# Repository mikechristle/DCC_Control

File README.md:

# DCC_Control
A project that controls a DCC model train set.
## Python Source for the Pico
The python source files that run on the Raspberry PI Pico to control the DCC signal
## Python Source for the PC Control Program
THe python source files that run on a PC to communicate with the Raspberry PI Pico.
## KiCad PCB Files
KiCad source files for the printed circuit board.
## Sources for the DCC_Monitor application
Sources for a seperate project that will monitor and display the contents of the DCC signal.

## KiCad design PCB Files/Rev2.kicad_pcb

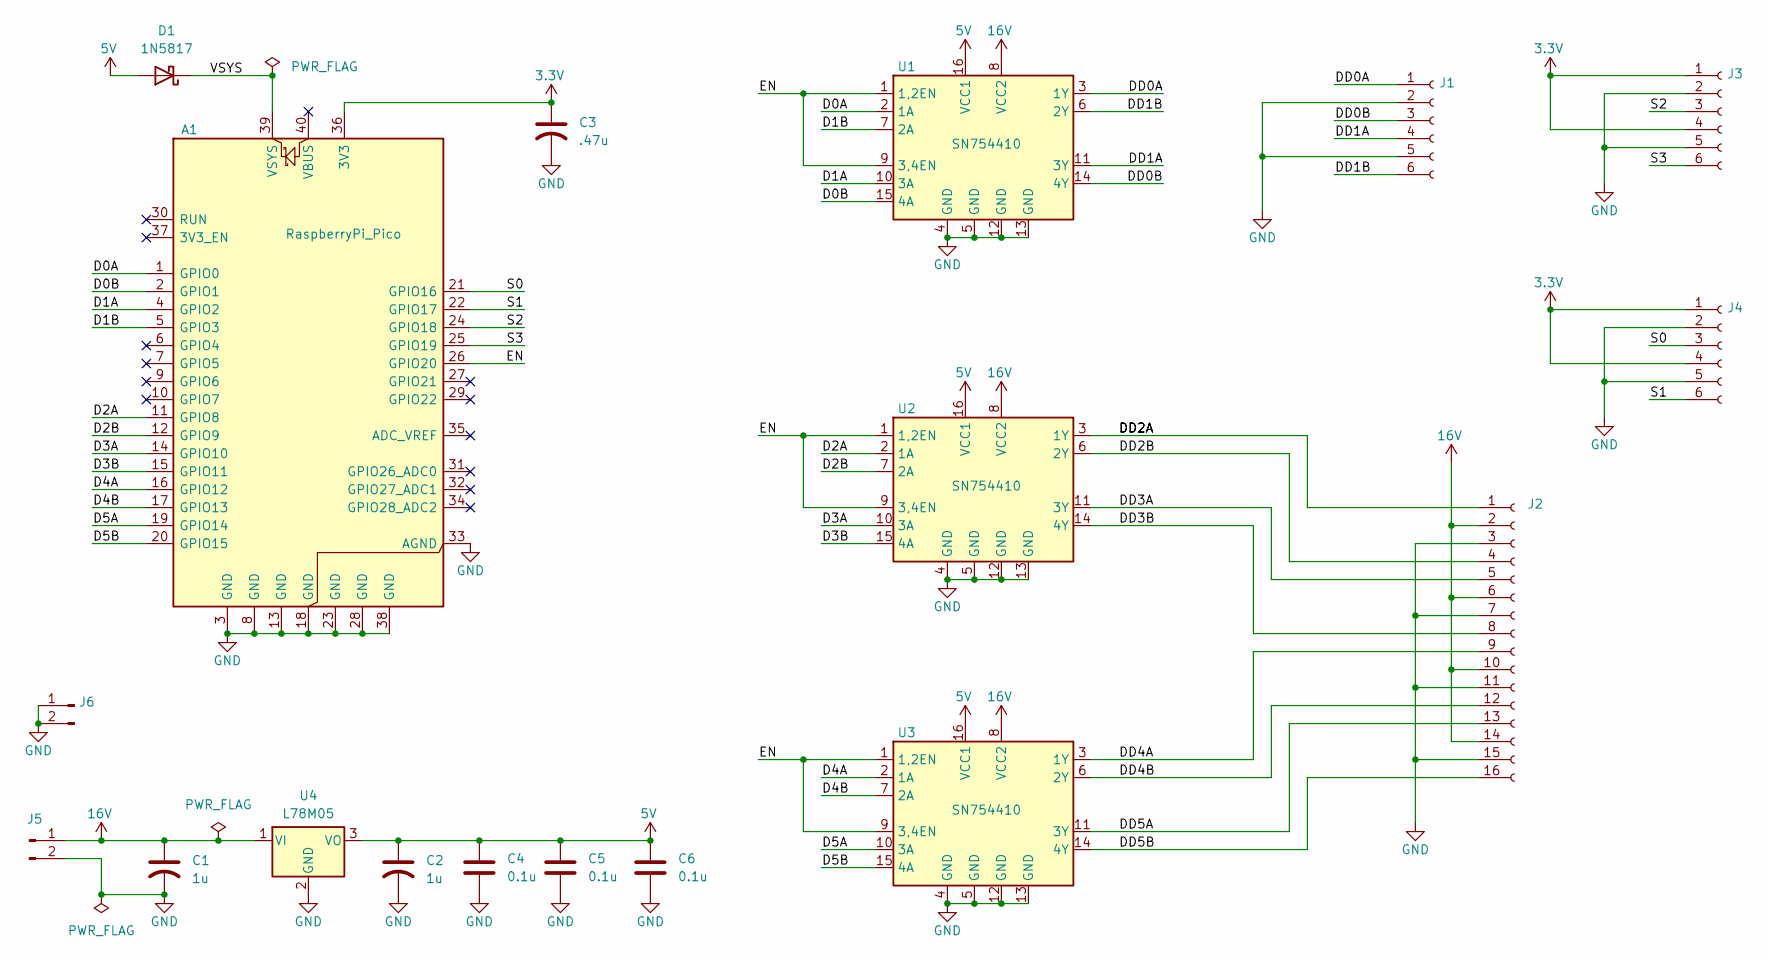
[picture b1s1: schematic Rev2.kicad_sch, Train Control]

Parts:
A1: RaspberryPi_Pico; DIP-40_700_ELL
C1, C2: 1u; CP_Radial_D6.3mm_P2.50mm
C3: .47u; CP_Radial_D6.3mm_P2.50mm
C4, C5, C6: 0.1u; C_Disc_D3.0mm_W1.6mm_P2.50mm
D1: 1N5817; D_A-405_P10.16mm_Horizontal
J1, J3, J4: Conn_01x06_Socket; Phoenix Socket 6
J2: Conn_01x16_Socket; Phoenix Socket 16
J5: 16Vdc; PinHeader_1x02_P2.54mm_Vertical
J6: GND; PinHeader_1x02_P2.54mm_Vertical
U1, U2, U3: SN754410; DIP-16_W7.62mm
U4: L78M05; TO-252-2

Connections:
3.3V: A1.36 (3V3), C3.1, J3.1, J3.4, J4.1, J4.4
5V: C2.1, C4.1, C5.1, C6.1, D1.2 (A), U1.16 (VCC1), U2.16 (VCC1), U3.16 (VCC1), U4.3 (VO)
16V: C1.1, J2.2, J2.6, J2.10, J2.14, J5.1, U1.8 (VCC2), U2.8 (VCC2), U3.8 (VCC2), U4.1 (VI)
/D0A: A1.1 (GPIO0), U1.2 (1A)
/D0B: A1.2 (GPIO1), U1.15 (4A)
/D1A: A1.4 (GPIO2), U1.10 (3A)
/D1B: A1.5 (GPIO3), U1.7 (2A)
/D2A: A1.11 (GPIO8), U2.2 (1A)
/D2B: A1.12 (GPIO9), U2.7 (2A)
/D3A: A1.14 (GPIO10), U2.10 (3A)
/D3B: A1.15 (GPIO11), U2.15 (4A)
/D4A: A1.16 (GPIO12), U3.2 (1A)
/D4B: A1.17 (GPIO13), U3.7 (2A)
/D5A: A1.19 (GPIO14), U3.10 (3A)
/D5B: A1.20 (GPIO15), U3.15 (4A)
/DD0A: J1.1, U1.3 (1Y)
/DD0B: J1.3, U1.14 (4Y)
/DD1A: J1.4, U1.11 (3Y)
/DD1B: J1.6, U1.6 (2Y)
/EN: A1.26 (GPIO20), U1.1 (1,2EN), U1.9 (3,4EN), U2.1 (1,2EN), U2.9 (3,4EN), U3.1 (1,2EN), U3.9 (3,4EN)
/S0: A1.21 (GPIO16), J4.3
/S1: A1.22 (GPIO17), J4.6
/S2: A1.24 (GPIO18), J3.3
/S3: A1.25 (GPIO19), J3.6
GND: A1.3 (GND), A1.8 (GND), A1.13 (GND), A1.18 (GND), A1.23 (GND), A1.28 (GND), A1.33 (AGND), A1.38 (GND), C1.2, C2.2, C3.2, C4.2, C5.2, C6.2, J1.2, J1.5, J2.3, J2.7, J2.11, J2.15, J3.2, J3.5, J4.2, J4.5, J5.2, J6.1, J6.2, U1.4 (GND), U1.5 (GND), U1.12 (GND), U1.13 (GND), U2.4 (GND), U2.5 (GND), U2.12 (GND), U2.13 (GND), U3.4 (GND), U3.5 (GND), U3.12 (GND), U3.13 (GND), U4.2 (GND)
unnamed: A1.39 (VSYS), D1.1 (K)
unnamed: J2.1, U2.3 (1Y)
unnamed: J2.4, U2.6 (2Y)
unnamed: J2.5, U2.11 (3Y)
unnamed: J2.8, U2.14 (4Y)
unnamed: J2.9, U3.3 (1Y)
unnamed: J2.12, U3.6 (2Y)
unnamed: J2.13, U3.11 (3Y)
unnamed: J2.16, U3.14 (4Y)

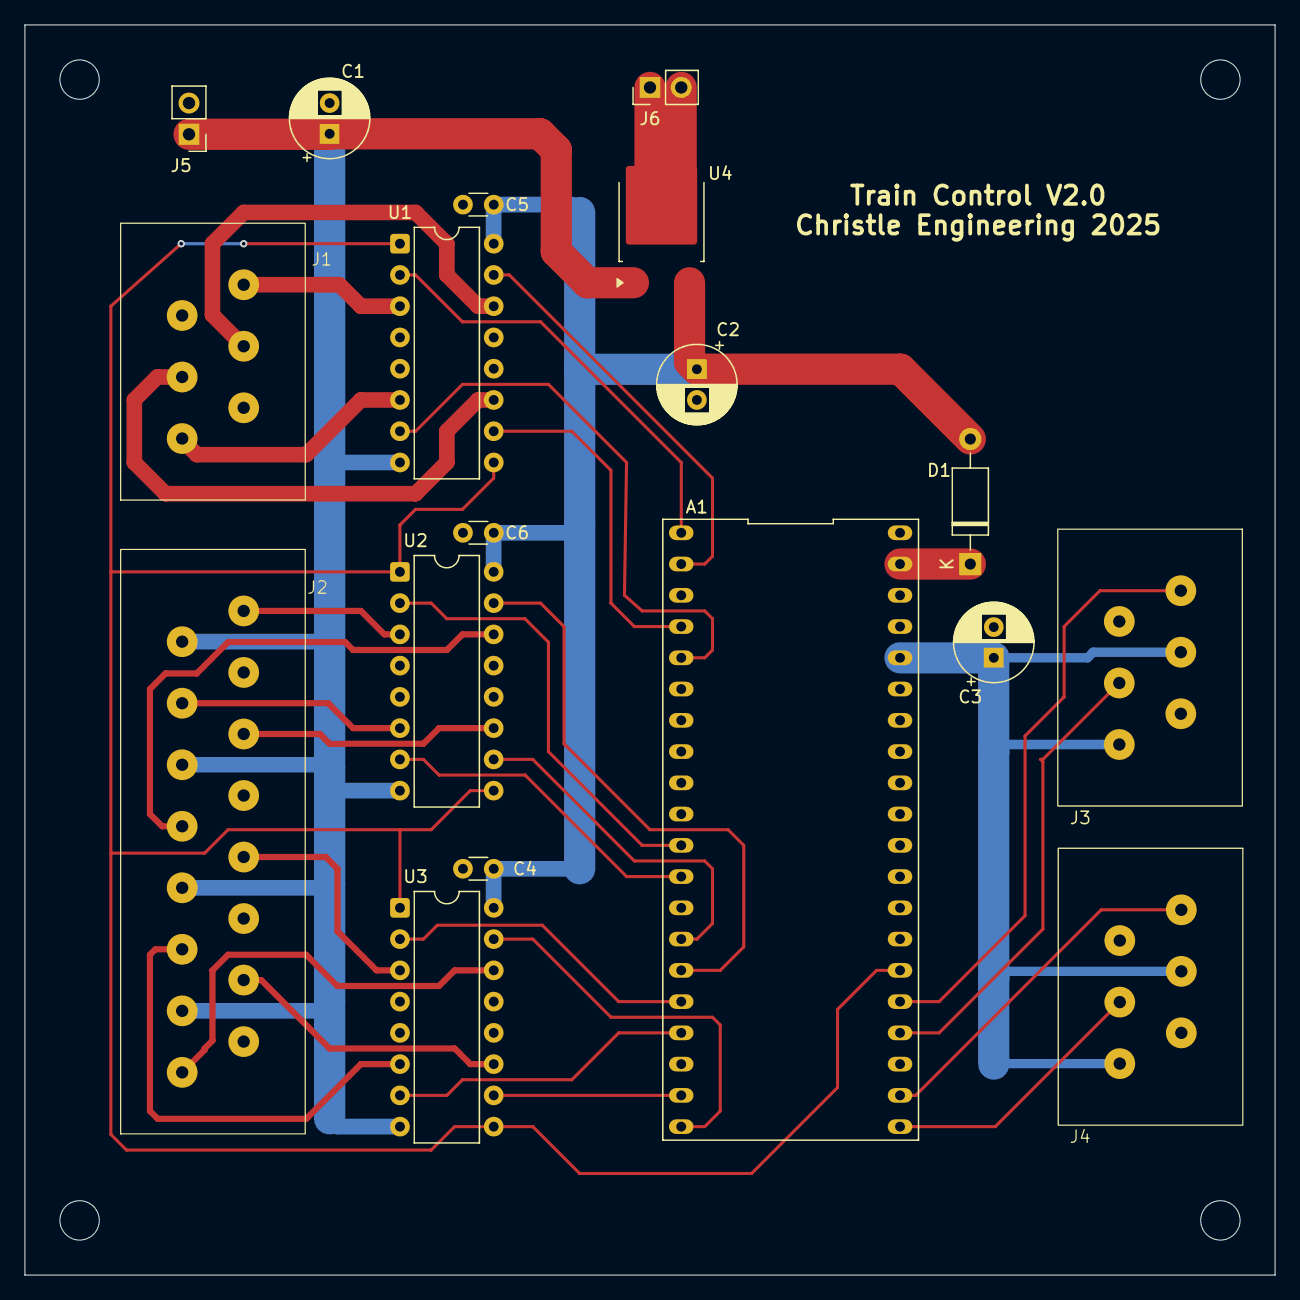
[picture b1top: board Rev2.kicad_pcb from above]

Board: 2 copper layers, 101.6 x 101.6 mm, 22 parts (0 on the bottom side), 34 nets.

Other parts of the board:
H1, H2, H3, H4: MountingHole_3.2mm_M3_ISO14580

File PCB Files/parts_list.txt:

Parts List

Designation Description                 Digikey PN
A1          Raspberry Pi Pico           SC0915
C1 C2       Cap 1 uF
C3          Cap 0.47 uF
C4 C5 C6    Cap 0.1 uF
D1          Schottky Diode 1N5817       497-4547-1-ND
U1 U2 U3    Half-H Driver SN754410      296-9911-5-ND
U4          Voltage Regulator L78M05    497-1203-1-ND
J1 J3 J4    6 Wire Connector            277-1798-ND
J2          16 Wire Connector           277-1808-ND
J5 J6       2 Pin Connector

            Hall Effect Sensor          96-DRV5032FALPGMCT-ND
            Magnet                      469-8905-ND

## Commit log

2026-03-03 Update README.md
    Add all file descriptions.
2026-03-03 Update README.md
    Remove specific file names.
2026-03-03 Create dcc_driver.py
    Initial release.
2026-03-03 Add files via upload
    Initial release.
2026-03-03 Create tracks.py
    Initial release.
2026-03-03 Create parts_list.txt
    Initial release.
2026-03-03 Create dcc_monitor_main.py
    Initial release.
